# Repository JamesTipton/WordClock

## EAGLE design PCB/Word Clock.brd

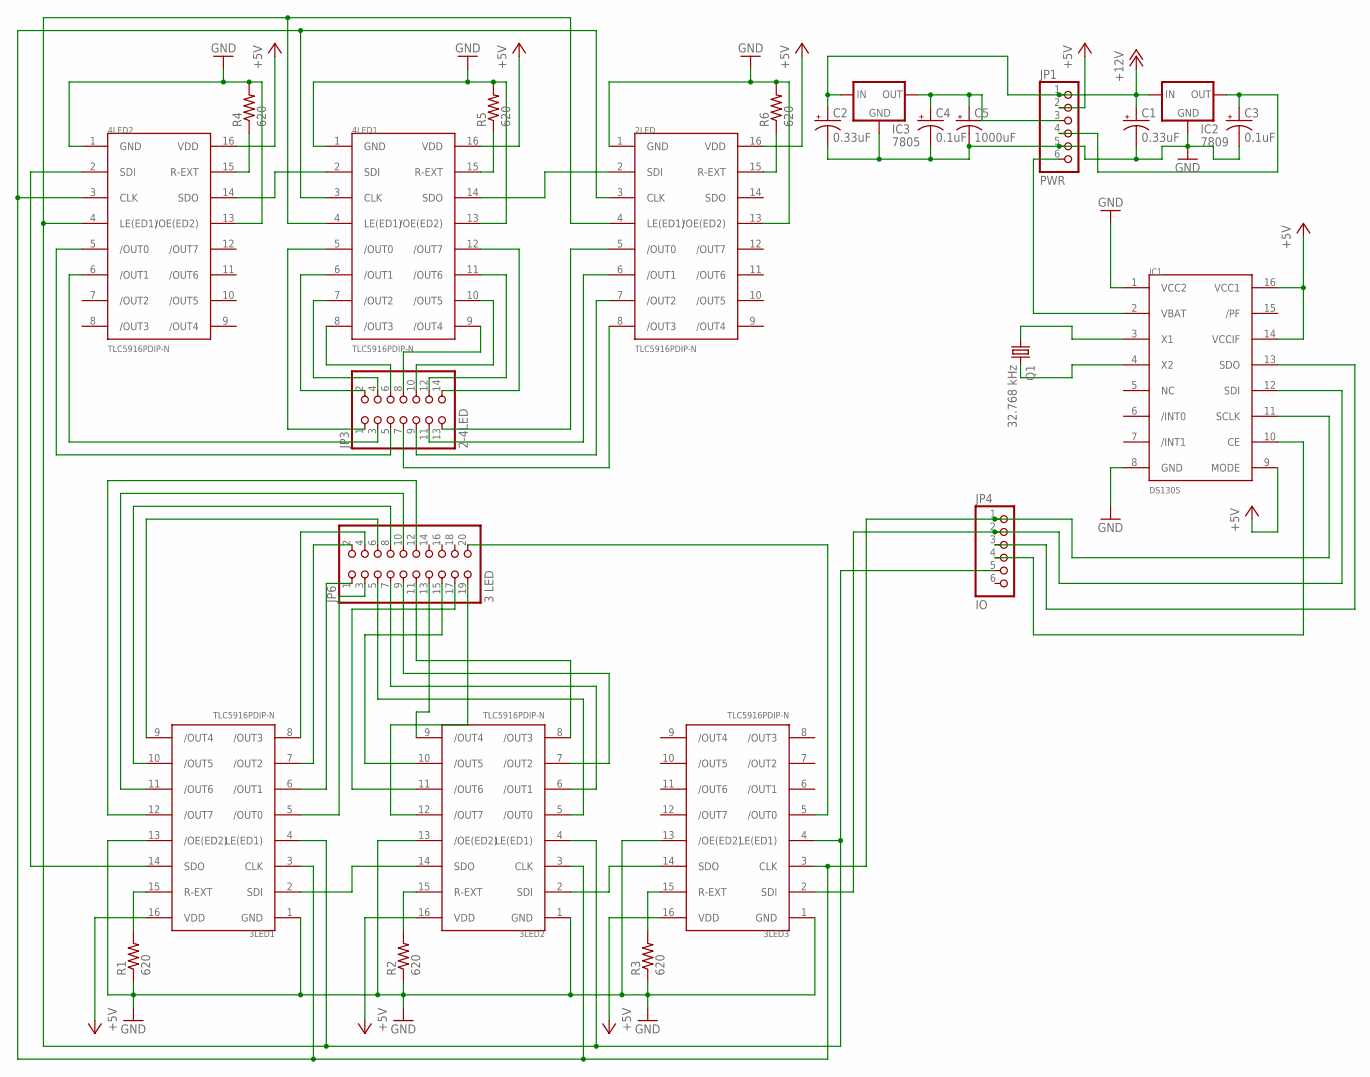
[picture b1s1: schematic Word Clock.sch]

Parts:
2LED, 3LED1, 3LED2, 3LED3, 4LED1, 4LED2: TLC5916PDIP-N; DIL16
C1, C2: 0.33uF; E2-4
C3, C4: 0.1uF; E2-4
C5: 1000uF; E3,5-8
IC1: DS1305; DIL16
IC2: 7809; 78XXL
IC3: 7805; 78XXL
JP1: PWR; 1X06
JP3: 2-4LED; 2X07
JP4: IO; 1X06
JP6: 3 LED; 2X10
Q1: 32.768 kHz; TC26V
R1, R2, R3, R4, R5, R6: 620; V235/17

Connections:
+5V: 2LED.16 (VDD), 3LED1.16 (VDD), 3LED2.16 (VDD), 3LED3.16 (VDD), 4LED1.16 (VDD), 4LED2.16 (VDD), IC1.9 (MODE), IC1.14 (VCCIF), IC1.16 (VCC1), JP1.2
+12V: C1.+, C2.+, IC2.IN, IC3.IN, JP1.1
GND: 2LED.1 (GND), 2LED.13 (/OE(ED2)), 3LED1.1 (GND), 3LED1.13 (/OE(ED2)), 3LED2.1 (GND), 3LED2.13 (/OE(ED2)), 3LED3.1 (GND), 3LED3.13 (/OE(ED2)), 4LED1.1 (GND), 4LED1.13 (/OE(ED2)), 4LED2.1 (GND), 4LED2.13 (/OE(ED2)), C1.-, C2.-, C3.-, C4.-, C5.-, IC1.1 (VCC2), IC1.8 (GND), IC2.GND, IC3.GND, JP1.5, R1.1, R2.1, R3.1, R4.2, R5.2, R6.2
MISO: IC1.13 (SDO), JP4.3
MOSI: 3LED3.2 (SDI), IC1.12 (SDI), JP4.2
unnamed: IC1.3 (X1), Q1.1
unnamed: IC1.4 (X2), Q1.2
unnamed: 2LED.5 (/OUT0), JP3.13
unnamed: 2LED.6 (/OUT1), JP3.11
unnamed: IC1.2 (VBAT), JP1.6
unnamed: 2LED.7 (/OUT2), JP3.9
unnamed: C4.+, C5.+, IC3.OUT, JP1.3
unnamed: C3.+, IC2.OUT, JP1.4
unnamed: 2LED.8 (/OUT3), JP3.7
unnamed: 4LED1.12 (/OUT7), JP3.14
unnamed: 4LED1.11 (/OUT6), JP3.12
unnamed: 4LED1.10 (/OUT5), JP3.10
unnamed: 4LED1.9 (/OUT4), JP3.8
unnamed: 4LED1.8 (/OUT3), JP3.6
unnamed: 4LED1.7 (/OUT2), JP3.4
unnamed: 4LED1.6 (/OUT1), JP3.2
unnamed: 4LED1.5 (/OUT0), JP3.1
unnamed: 4LED2.6 (/OUT1), JP3.3
unnamed: 4LED2.5 (/OUT0), JP3.5
unnamed: 2LED.2 (SDI), 4LED1.14 (SDO)
unnamed: 4LED1.2 (SDI), 4LED2.14 (SDO)
unnamed: 3LED1.12 (/OUT7), JP6.12
unnamed: 3LED1.7 (/OUT2), JP6.2
unnamed: 3LED1.8 (/OUT3), JP6.4
unnamed: 3LED1.9 (/OUT4), JP6.6
unnamed: 4LED2.15 (R-EXT), R4.1
unnamed: 4LED1.15 (R-EXT), R5.1
unnamed: 2LED.15 (R-EXT), R6.1
unnamed: 3LED1.10 (/OUT5), JP6.8
unnamed: 3LED1.11 (/OUT6), JP6.10
unnamed: 3LED2.5 (/OUT0), JP6.5
unnamed: 3LED3.5 (/OUT0), JP6.20
unnamed: 3LED2.6 (/OUT1), JP6.7
unnamed: 3LED2.7 (/OUT2), JP6.9
unnamed: 2LED.4 (LE(ED1)), 3LED1.4 (LE(ED1)), 3LED2.4 (LE(ED1)), 3LED3.4 (LE(ED1)), 4LED1.4 (LE(ED1)), 4LED2.4 (LE(ED1)), JP4.5
unnamed: 3LED1.6 (/OUT1), JP6.1
unnamed: 3LED1.5 (/OUT0), JP6.3
unnamed: 3LED2.8 (/OUT3), JP6.11
unnamed: 3LED2.9 (/OUT4), JP6.13
unnamed: 3LED2.10 (/OUT5), JP6.15
unnamed: 3LED2.11 (/OUT6), JP6.17
unnamed: 3LED2.12 (/OUT7), JP6.19
unnamed: 3LED2.2 (SDI), 3LED3.14 (SDO)
unnamed: 3LED1.2 (SDI), 3LED2.14 (SDO)
unnamed: 3LED1.14 (SDO), 4LED2.2 (SDI)
unnamed: 3LED3.15 (R-EXT), R3.2
unnamed: 3LED2.15 (R-EXT), R2.2
unnamed: 3LED1.15 (R-EXT), R1.2
SDI_CLK: 2LED.3 (CLK), 3LED1.3 (CLK), 3LED2.3 (CLK), 3LED3.3 (CLK), 4LED1.3 (CLK), 4LED2.3 (CLK), IC1.11 (SCLK), JP4.1
SS_RTC: IC1.10 (CE), JP4.4

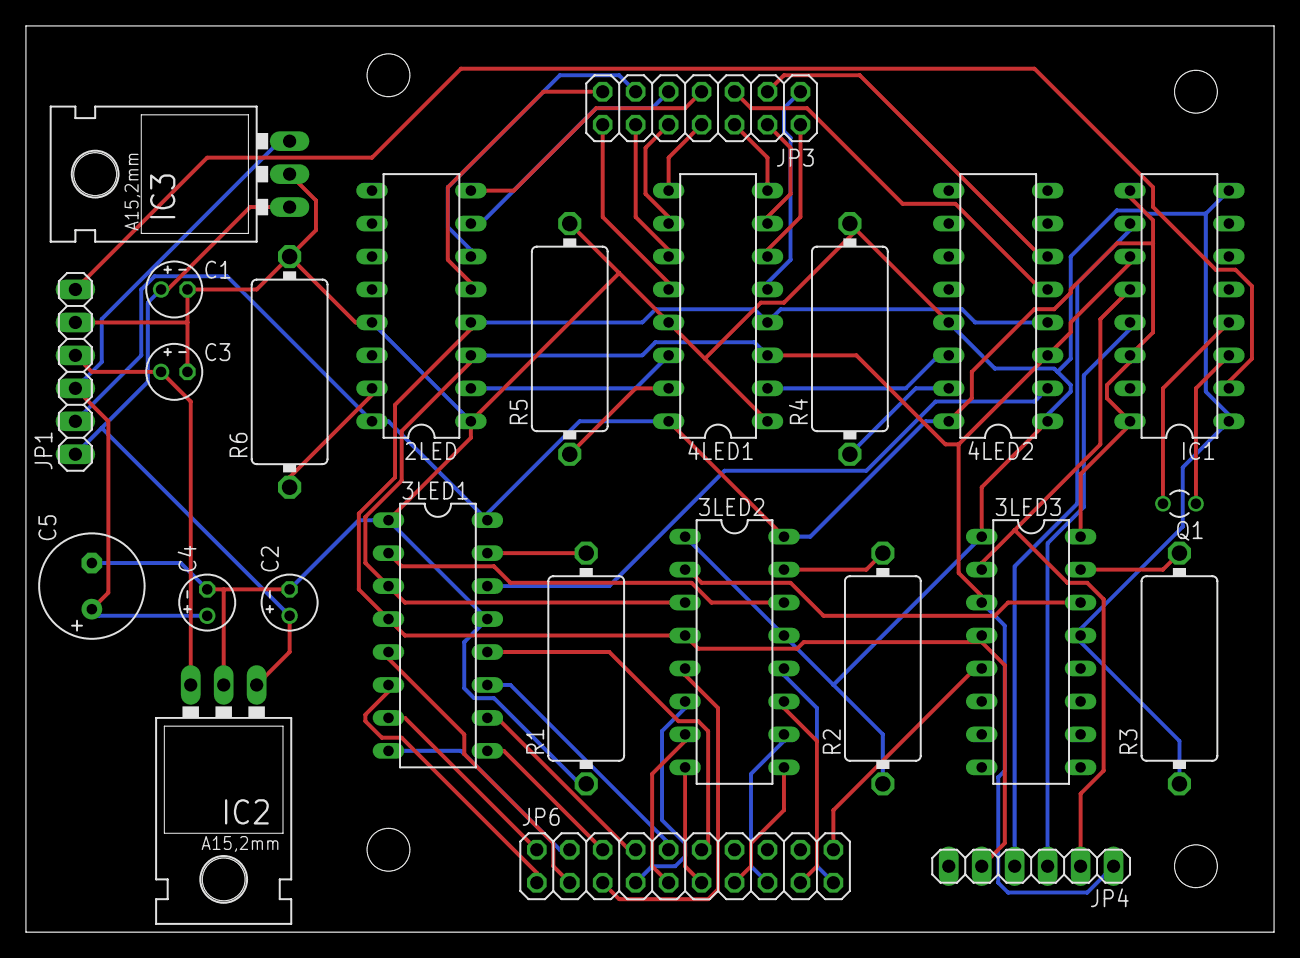
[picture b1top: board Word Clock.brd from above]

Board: 2 copper layers, 96.2 x 69.8 mm, 25 parts (0 on the bottom side), 55 nets.

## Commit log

2017-01-04 :octocat: Added .gitattributes & .gitignore files
2017-01-04 Initial Commit
    Commit of initial design documents and code
